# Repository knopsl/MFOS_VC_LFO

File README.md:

# MFOS VC LFO sync mod, pulse width fix, and Kosmo panel

This is a couple of modifications for the MFOS VC LFO and a Kosmo format front panel. One mod is component value changes, described below, that correct some undesired behavior having to do with the pulse width. The other is an auxiliary PCB that adds a sync input as well as a Euro/Kosmo style power header.

## Sync input

The auxiliary board adds a sync input. A rising edge on this input resets the LFO's triangle core to either the maximum or the minimum peak (switch selectable). This allows LFO modulation to begin in sync with e.g. the start of a note. Other outputs also are synced at either the "beginning" or the "midpoint" (in time) of the waveform.

This modification is based on Tim Parkhurst's [sync mod](https://electro-music.com/forum/post-387749.html#387749).  I added a switch to select whether to charge the triangle core to its maximum or minimum value, affecting where in each waveform sync occurs. Resistances were changed to accommodate the MFOS LFO's larger integrating capacitor, and I used J113 for the JFET instead of 2N3819. 2N5458 was also found to work, J112 did not. One resistor was made a trimmer to allow tuning the voltage to which the oscillator resets. It should be adjusted until the triangle wave is at its maximum or minimum immediately after syncing.

The auxiliary board also has footprints for a Eurorack style power header with reversal protection diodes and bypass capacitors (which should be mounted there instead of on the MFOS board) and a terminal block. Wires from the terminal block connect to ±12 V and ground on the MFOS board. Molex connectors are used to connect the sync mod to the panel controls and PCB.

## Pulse width fixes

As designed, the MFOS LFO has some undesireable behavior with the pulse width. The PW CV input floats when nothing is plugged in, meaning that the pulse width and its range are different with no CV input versus with 0V CV input. Also, since the PW pot and its associated fixed resistors are large compared to the summing resistors, an attenuator on the PW CV (external or added to the front panel) will affect the behavior of the pulse width pot and vice versa.

I recommend the following changes:

* R37 (pulse width pot) from 100k to 25k
* R36 and R42 (fixed resistors at ends of R37) from 100k to 3.3k
* R58 and R59 (summing resistors) from 10k to 200k

With these changes I find the effects of the PW pot on the PW CV attenuator and vice versa are negligible, and I get a pulse width range from the knob (with no CV) of about 7% to 91%. 

## Front panel

A Kosmo format front panel is also provided. It includes space for the attenuator pots for the FM 1 and PWM control voltages. Width is 10 cm.

## Sync mod documentation

* [Build notes](Docs/build_notes.md) 
* [BOM](Docs/MFOS_VCLFO_aux.pdf) (See above for changes to the main PCB BOM.)
* [Schematics](Docs/MFOS_VCLFO_aux.pdf)

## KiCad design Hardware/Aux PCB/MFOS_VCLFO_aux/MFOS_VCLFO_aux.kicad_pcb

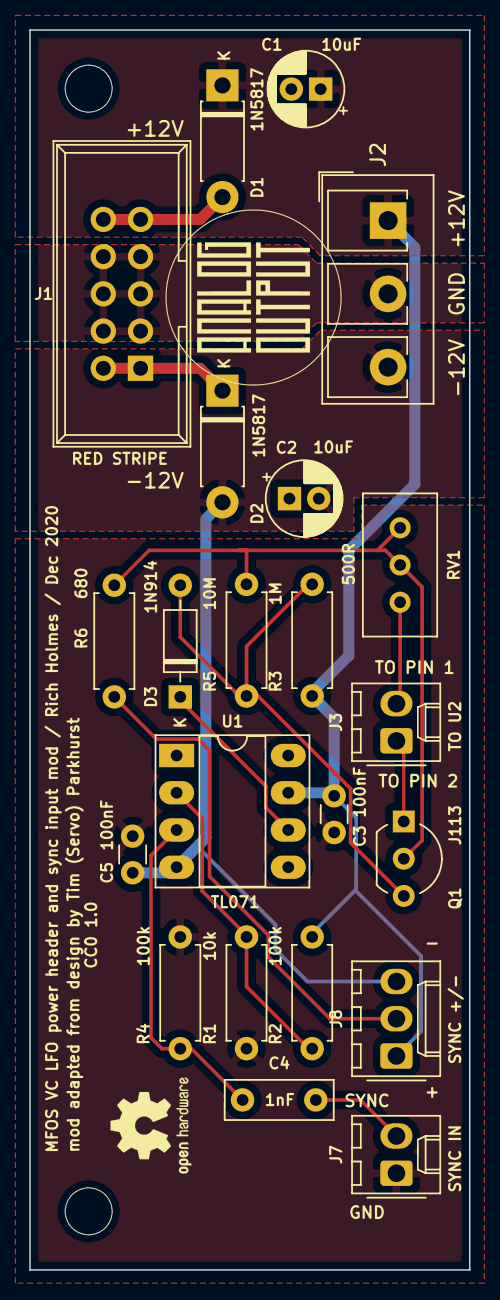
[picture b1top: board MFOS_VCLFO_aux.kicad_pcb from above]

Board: 2 copper layers, 30.0 x 84.6 mm, 26 parts (0 on the bottom side), 14 nets.

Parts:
C1, C2: 10uF; CP_Radial_D5.0mm_P2.00mm
C3, C5: 100nF; C_Disc_D3.0mm_W1.6mm_P2.50mm
C4: 1nF; C_Rect_L7.2mm_W2.5mm_P5.00mm_FKS2_FKP2_MKS2_MKP2
D1, D2: 1N5817; D_DO-41_SOD81_P7.62mm_Horizontal
D3: 1N914; D_DO-35_SOD27_P7.62mm_Horizontal
GRAF1: Graphic; analogoutput_12mm
GRAF2: Graphic; OSHW-Logo2_7.3x6mm_SilkScreen
H1, H2: MountingHole; MountingHole_3.2mm_M3
J1: Synth_power_2x5; Power_Header
J2: Screw_Terminal_01x03; TerminalBlock_Degson_DG301_1x03_P5.00mm_Vertical
J3, J7: 2 pin Molex header; Molex_KK-254_AE-6410-02A_1x02_P2.54mm_Vertical
J8: 3 pin Molex header; Molex_KK-254_AE-6410-03A_1x03_P2.54mm_Vertical
Q1: J113; TO-92_Inline_Wide
R1: 10k; R_Axial_DIN0207_L6.3mm_D2.5mm_P7.62mm_Horizontal
R2, R4: 100k; R_Axial_DIN0207_L6.3mm_D2.5mm_P7.62mm_Horizontal
R3: 1M; R_Axial_DIN0207_L6.3mm_D2.5mm_P7.62mm_Horizontal
R5: 10M; R_Axial_DIN0207_L6.3mm_D2.5mm_P7.62mm_Horizontal
R6: 680; R_Axial_DIN0207_L6.3mm_D2.5mm_P7.62mm_Horizontal
RV1: 500R; Potentiometer_Bourns_3296W_Vertical
U1: TL071; DIP-8_W7.62mm_Socket_LongPads

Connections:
+12V: C1.1, C3.2, D1.1, J2.1, J8.1, R2.2, R3.1, U1.7
-12V: C2.2, C5.2, D2.2, J2.3, J8.3, U1.4
/PIN1: J3.2, RV1.1
/PIN2: J3.1, Q1.1
GND: C1.2, C2.1, C3.1, C5.1, J1.3, J1.4, J1.5, J1.6, J1.7, J1.8, J2.2, J7.1, R1.1, R4.2
unnamed: C4.1, R4.1, U1.3
unnamed: C4.2, J7.2
unnamed: D1.2, J1.9, J1.10
unnamed: D2.1, J1.1, J1.2
unnamed: D3.1, U1.6
unnamed: D3.2, Q1.3, R3.2, R5.1
unnamed: J8.2, R6.2
unnamed: Q1.2, R5.2, R6.1, RV1.2, RV1.3
unnamed: R1.2, R2.1, U1.2

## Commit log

2020-12-28 Initial version
2020-12-28 Create LICENSE
2020-12-28 Add panel image to README
2020-12-28 Fix path
2021-01-17 Include lib table files; new Gerbers
2021-02-13 BOM and some symbol work, .gitignore_extra
2021-02-19 Backlog
2021-02-28 Update .gitignore, DIN5
2021-03-02 Extraneous stuff out of .gitignore
2021-03-02 rm dumb file
2021-03-02 Make C4 film, correct dumbass op amp topology
2021-03-02 Add some PCB labels
2021-03-31 Final revisions before fabrication
2021-04-10 BOM updates
2021-04-12 Update documentation
2021-04-12 Correct updated documentation
2021-04-14 Revised Gerbers
2021-04-24 Move images, add link to wiring diagram to READMS
2021-04-26 Docs improvements
2021-08-07 Kosmo_panel lib update
2021-09-06 Fix bad link in README
